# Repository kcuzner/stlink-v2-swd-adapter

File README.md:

# STLink-v2 SWD Adapter

All of my projects use this tiny 4-pin JST-SH connector for their SWD and reset connection. I have been using a
dangling-wire adapter plugged into a breadboard, but that has started to break. This is a small (<1"sq) PCB which takes
the pinout from my STLink-v2 and just runs it out to a JST-SH connector and a reset button. I've added some header
options for rewiring the order of the pins if needed.

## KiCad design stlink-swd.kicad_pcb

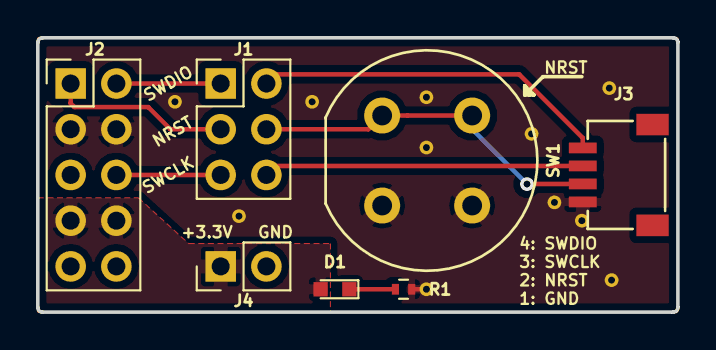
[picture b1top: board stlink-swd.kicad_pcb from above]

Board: 2 copper layers, 35.6 x 15.2 mm, 7 parts (0 on the bottom side), 9 nets.

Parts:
D1: LED; LED_0603
J1: Conn_02x03_Odd_Even; Pin_Header_Straight_2x03_Pitch2.54mm
J2: Ribbon IDC DIP; Pin_Header_Straight_2x05_Pitch2.54mm
J3: SWD-RA; JST-SH-4-RA
J4: Conn_01x02; Pin_Header_Straight_1x02_Pitch2.54mm
R1: R; R_0402
SW1: KS-00Q-02; Push_E-Switch_KS01Q01

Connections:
+3V3: D1.2, J2.7, J2.8, J4.1
/NRST: J1.3, J2.1
/NRST_JST: J1.4, J3.2, SW1.1
/SWCLK: J1.5, J2.6
/SWCLK_JST: J1.6, J3.3
/SWDIO: J1.1, J2.2
/SWDIO_JST: J1.2, J3.4
GND: J2.3, J2.4, J3.1, J4.2, R1.2, SW1.2
unnamed: D1.1, R1.1

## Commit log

2019-01-11 Added part numbers and rounded PCB edges
    Also deleted some temporary BOM files that got checked in.
2019-01-11 Gerbers ordered
2019-01-12 Added readme and license
2019-01-12 Saving the PCB after gerber export
